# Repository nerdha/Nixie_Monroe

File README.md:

Nixie_Monroe
============

Boards and code for the nixie clock I made from the tubes of an old Monroe 610 calculator and a log reclaimed from a tree destroyed by Hurricane Sandy.

http://www.flickr.com/photos/hmason/8914375124/

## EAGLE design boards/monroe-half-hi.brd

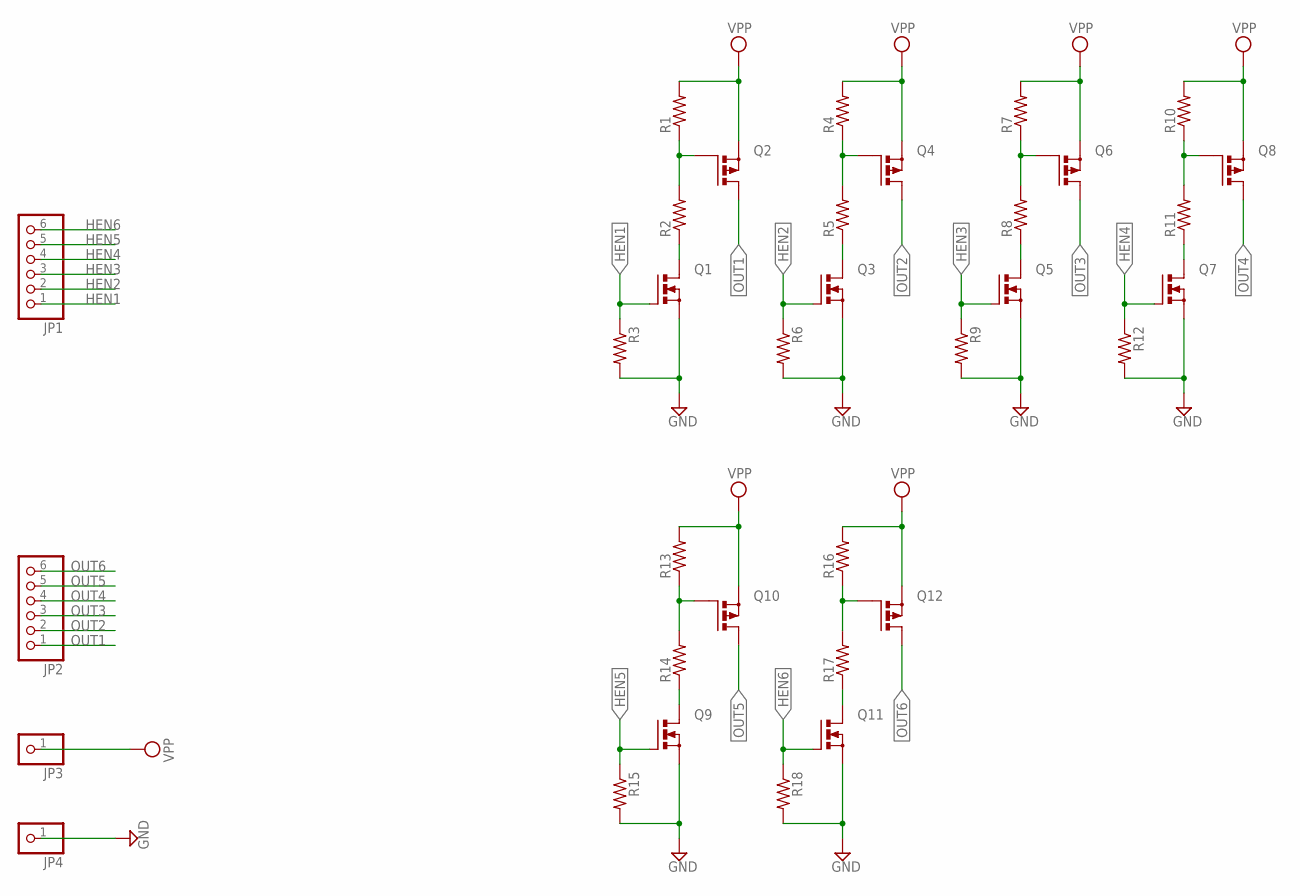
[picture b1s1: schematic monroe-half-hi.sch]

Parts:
JP1, JP2: PINHD-1X6; 1X06
JP3, JP4: PINHD-1X1; 1X01
Q1, Q3, Q5, Q7, Q9, Q11: PMOSFET_NTO220BV; TO220BV
Q2, Q4, Q6, Q8, Q10, Q12: PMOSFET_PTO220BV; TO220BV
R1, R3, R4, R6, R7, R9, R10, R12, R13, R15, R16, R18: R-US_0207/5V; 0207/5V
R2, R5, R8, R11, R14, R17: R-US_0207/10; 0207/10

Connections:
GND: JP4.1, Q1.S, Q3.S, Q5.S, Q7.S, Q9.S, Q11.S, R3.2, R6.2, R9.2, R12.2, R15.2, R18.2
HEN1: JP1.1, Q1.G, R3.1
HEN2: JP1.2, Q3.G, R6.1
HEN3: JP1.3, Q5.G, R9.1
HEN4: JP1.4, Q7.G, R12.1
HEN5: JP1.5, Q9.G, R15.1
HEN6: JP1.6, Q11.G, R18.1
unnamed: Q2.G, R1.1, R2.2
unnamed: Q1.D, R2.1
unnamed: Q4.G, R4.1, R5.2
unnamed: Q3.D, R5.1
unnamed: Q6.G, R7.1, R8.2
unnamed: Q5.D, R8.1
unnamed: Q8.G, R10.1, R11.2
unnamed: Q7.D, R11.1
unnamed: Q10.G, R13.1, R14.2
unnamed: Q9.D, R14.1
unnamed: Q12.G, R16.1, R17.2
unnamed: Q11.D, R17.1
OUT1: JP2.1, Q2.D
OUT2: JP2.2, Q4.D
OUT3: JP2.3, Q6.D
OUT4: JP2.4, Q8.D
OUT5: JP2.5, Q10.D
OUT6: JP2.6, Q12.D
VPP: JP3.1, Q2.S, Q4.S, Q6.S, Q8.S, Q10.S, Q12.S, R1.2, R4.2, R7.2, R10.2, R13.2, R16.2

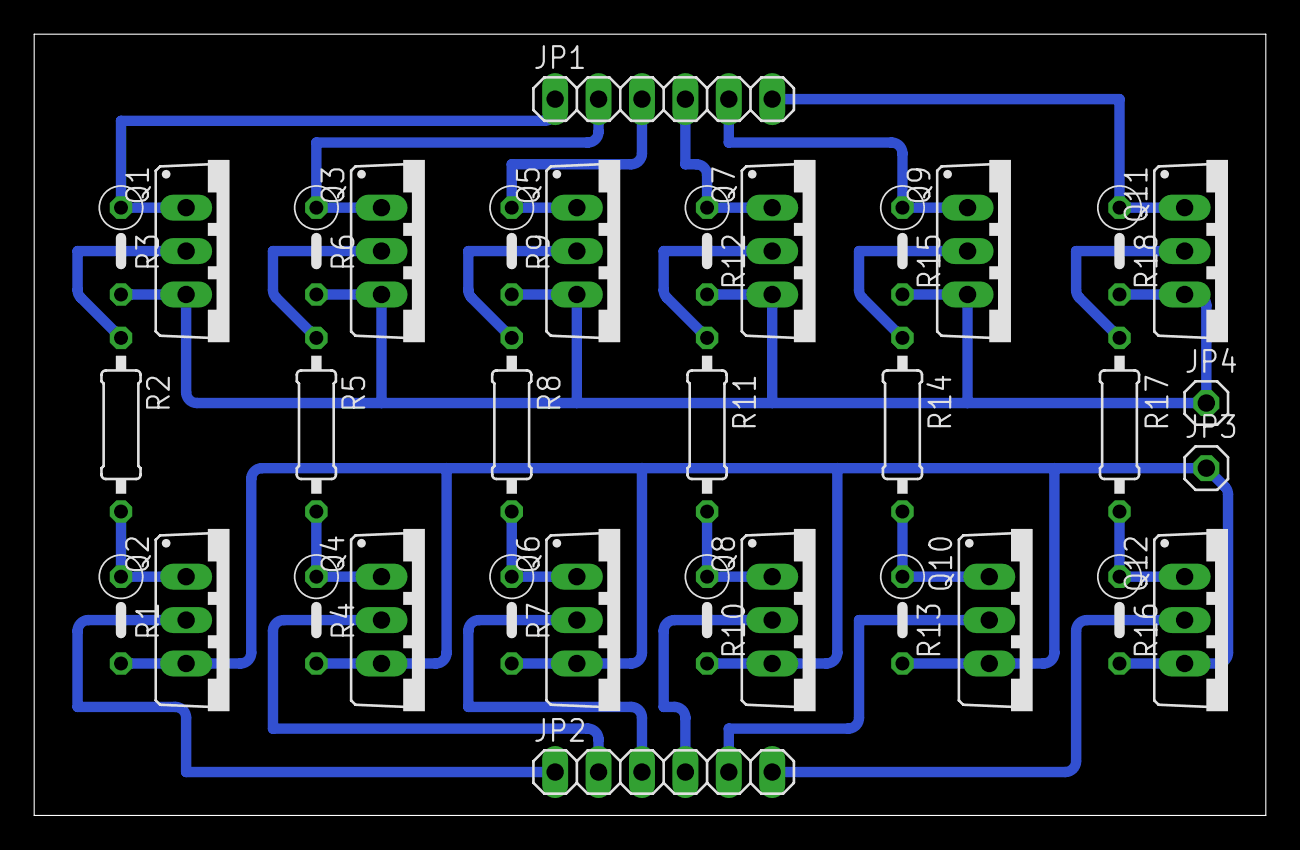
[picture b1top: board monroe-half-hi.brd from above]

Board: 2 copper layers, 72.1 x 45.7 mm, 34 parts (0 on the bottom side), 26 nets.

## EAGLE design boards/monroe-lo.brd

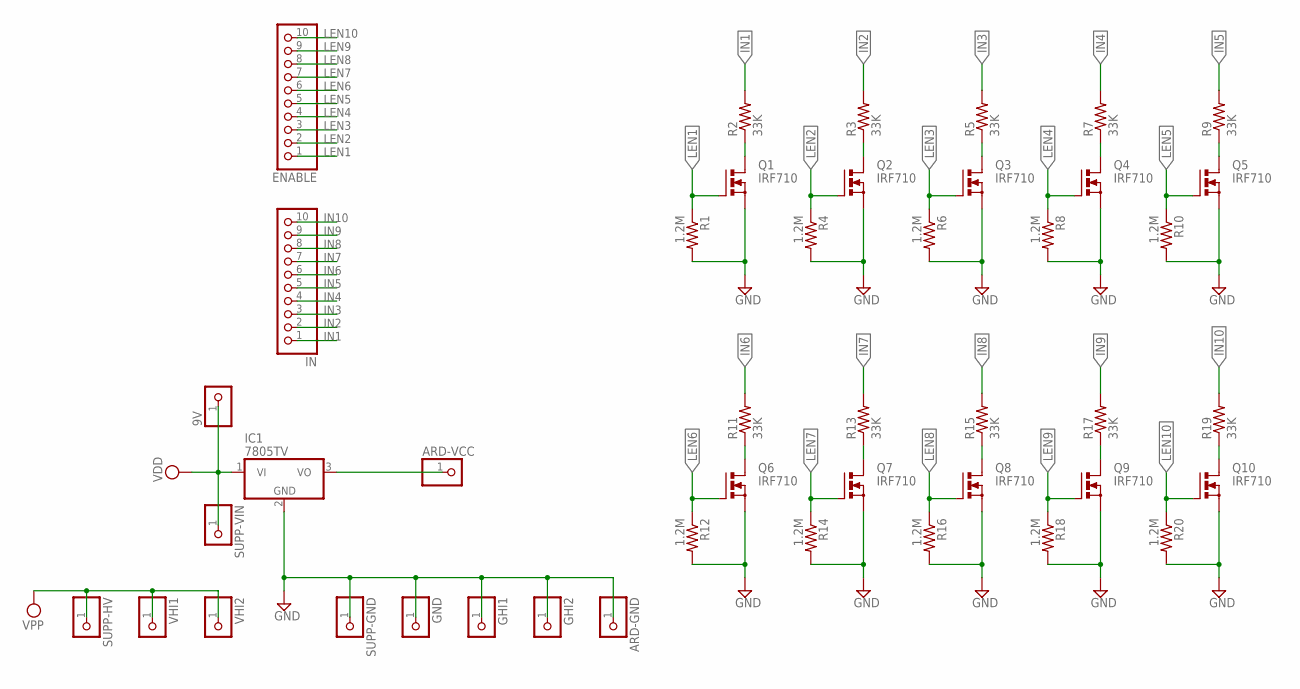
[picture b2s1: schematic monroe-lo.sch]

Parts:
9V: PINHD-1X1; 1X01
ARD-GND: PINHD-1X1; 1X01
ARD-VCC: PINHD-1X1; 1X01
ENABLE: PINHD-1X10; 1X10
GHI1, GHI2: PINHD-1X1; 1X01
GND: PINHD-1X1; 1X01
IC1: 7805TV; TO220V
IN: PINHD-1X10; 1X10
Q1, Q2, Q3, Q4, Q5, Q6, Q7, Q8, Q9, Q10: IRF710; TO220BV
R1, R4, R6, R8, R10, R12, R14, R16, R18, R20: 1.2M; 0207/2V
R2, R3, R5, R7, R9, R11, R13, R15, R17, R19: 33K; 0207/7
SUPP-GND: PINHD-1X1; 1X01
SUPP-HV: PINHD-1X1; 1X01
SUPP-VIN: PINHD-1X1; 1X01
VHI1, VHI2: PINHD-1X1; 1X01

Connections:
GND: ARD-GND.1, GHI1.1, GHI2.1, GND.1, IC1.2 (GND), Q1.S, Q2.S, Q3.S, Q4.S, Q5.S, Q6.S, Q7.S, Q8.S, Q9.S, Q10.S, R1.2, R4.2, R6.2, R8.2, R10.2, R12.2, R14.2, R16.2, R18.2, R20.2, SUPP-GND.1
IN1: IN.1, R2.2
IN2: IN.2, R3.2
IN3: IN.3, R5.2
IN4: IN.4, R7.2
IN5: IN.5, R9.2
IN6: IN.6, R11.2
IN7: IN.7, R13.2
IN8: IN.8, R15.2
IN9: IN.9, R17.2
IN10: IN.10, R19.2
LEN1: ENABLE.1, Q1.G, R1.1
LEN2: ENABLE.2, Q2.G, R4.1
LEN3: ENABLE.3, Q3.G, R6.1
LEN4: ENABLE.4, Q4.G, R8.1
LEN5: ENABLE.5, Q5.G, R10.1
LEN6: ENABLE.6, Q6.G, R12.1
LEN7: ENABLE.7, Q7.G, R14.1
LEN8: ENABLE.8, Q8.G, R16.1
LEN9: ENABLE.9, Q9.G, R18.1
LEN10: ENABLE.10, Q10.G, R20.1
unnamed: Q2.D, R3.1
unnamed: Q1.D, R2.1
unnamed: Q3.D, R5.1
unnamed: Q4.D, R7.1
unnamed: Q5.D, R9.1
unnamed: Q6.D, R11.1
unnamed: Q7.D, R13.1
unnamed: Q8.D, R15.1
unnamed: Q9.D, R17.1
unnamed: Q10.D, R19.1
unnamed: ARD-VCC.1, IC1.3 (VO)
VDD: 9V.1, IC1.1 (VI), SUPP-VIN.1
VPP: SUPP-HV.1, VHI1.1, VHI2.1

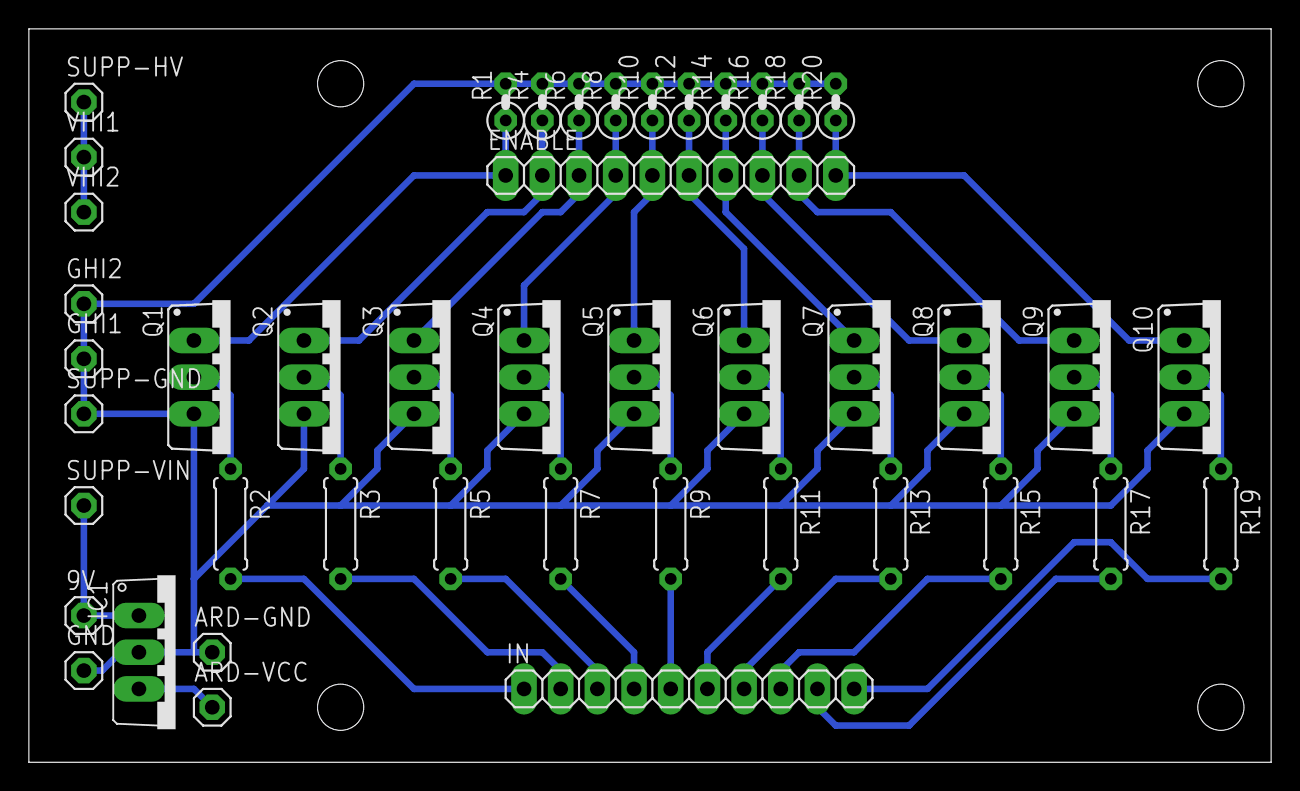
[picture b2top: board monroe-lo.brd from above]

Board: 2 copper layers, 86.0 x 50.8 mm, 44 parts (0 on the bottom side), 34 nets.

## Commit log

2013-01-19 initial comit
2013-01-20 commented and cleaned arduino sketch
2013-06-01 now with a human-readable clock!
2013-06-01 and now the knob controls the brightness
